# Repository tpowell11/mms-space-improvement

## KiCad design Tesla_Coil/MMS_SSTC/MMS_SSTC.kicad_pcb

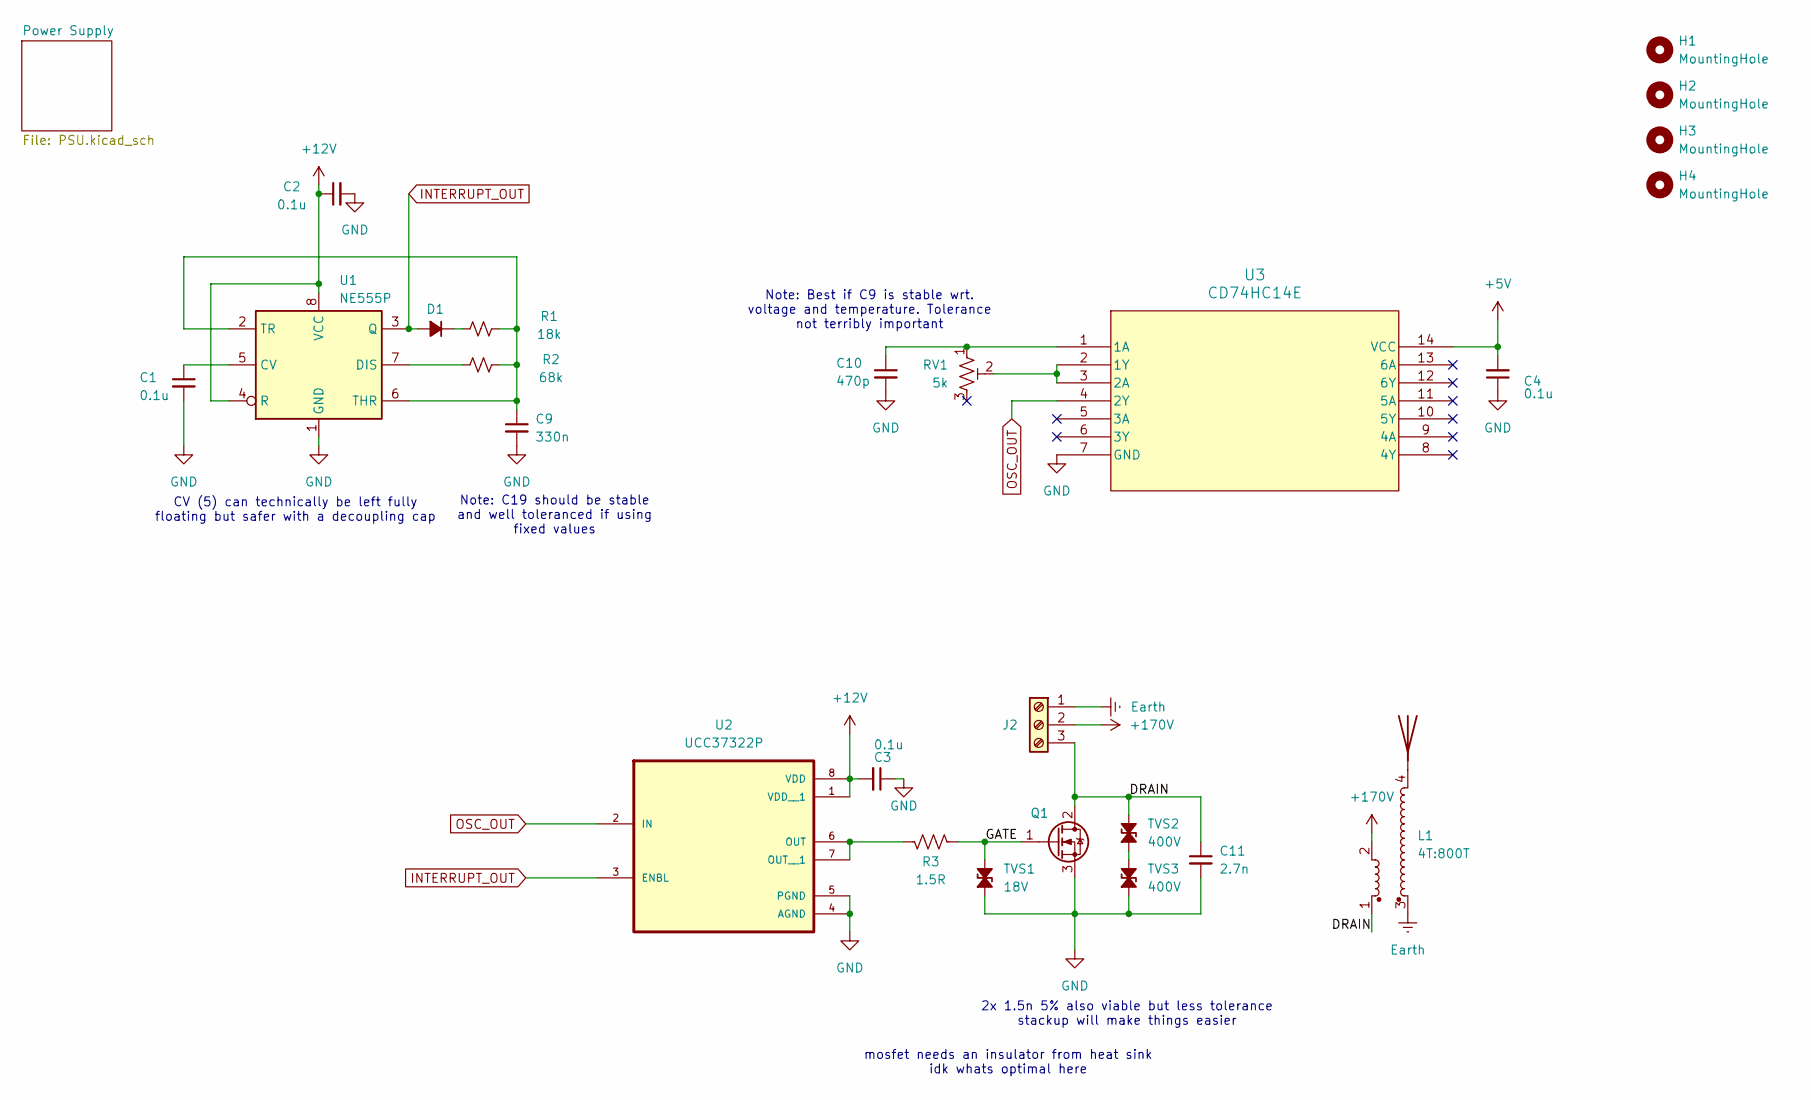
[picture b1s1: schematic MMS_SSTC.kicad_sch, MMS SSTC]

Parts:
AE1: Antenna
C1, C2, C3, C4: 0.1u; C_Disc_D3.0mm_W2.0mm_P2.50mm
C9: 330n; C_Rect_L7.2mm_W3.5mm_P5.00mm_FKS2_FKP2_MKS2_MKP2
C10: 470p; C_Rect_L7.2mm_W4.5mm_P5.00mm_FKS2_FKP2_MKS2_MKP2
C11: 2.7n; C_Rect_L13.0mm_W4.0mm_P10.00mm_FKS3_FKP3_MKS4
D1: D_Small_Filled; D_DO-35_SOD27_P7.62mm_Horizontal
H1, H2, H3, H4: MountingHole; MountingHole_3.2mm_M3
J2: Screw_Terminal_01x02; 691137710003
L1: 4T:800T
Q1: FQA8N100C; TO-247-3_Vertical
R1: 18k; R_Axial_DIN0204_L3.6mm_D1.6mm_P5.08mm_Horizontal
R2: 68k; R_Axial_DIN0204_L3.6mm_D1.6mm_P5.08mm_Horizontal
R3: 1.5R; R_Axial_DIN0204_L3.6mm_D1.6mm_P5.08mm_Horizontal
RV1: 5k; Potentiometer_Bourns_3296X_Horizontal
TVS1: 18V; D_DO-27_P12.70mm_Horizontal
TVS2, TVS3: 400V; D_DO-27_P12.70mm_Horizontal
U1: NE555P; DIP-8_W7.62mm_Socket
U2: UCC37322P; DIP-8_W7.62mm_Socket
U3: CD74HC14E; DIP-14_W7.62mm_Socket

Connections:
+5V: C4.2, U3.14 (VCC); also elsewhere on the board
+12V: C2.1, C3.2, U1.4 (R), U1.8 (VCC), U2.1 (VDD__1), U2.8 (VDD); also elsewhere on the board
+170V: J2.2, L1.2; also elsewhere on the board
/DRAIN: C11.1, J2.3, L1.1, Q1.2 (D), TVS2.2 (A2)
/GATE: Q1.1 (G), R3.1, TVS1.2 (A2)
Earth: J2.1, L1.3; also elsewhere on the board
GND: C1.2, C2.2, C3.1, C4.1, C9.2, C10.2, C11.2, Q1.3 (S), TVS1.1 (A1), TVS3.1 (A1), U1.1 (GND), U2.4 (AGND), U2.5 (PGND), U3.7 (GND); also elsewhere on the board
INTERRUPT_OUT: D1.2 (A), U1.3 (Q), U2.3 (ENBL)
unnamed: AE1.1, L1.4
unnamed: D1.1 (K), R1.1
unnamed: TVS2.1 (A1), TVS3.2 (A2)
unnamed: C1.1, U1.5 (CV)
unnamed: R2.1, U1.7 (DIS)
unnamed: C9.1, R1.2, R2.2, U1.2 (TR), U1.6 (THR)
unnamed: R3.2, U2.6 (OUT), U2.7 (OUT__1)
unnamed: C10.1, RV1.1, U3.1 (1A)
unnamed: RV1.2, U3.2 (1Y), U3.3 (2A)
OSC_OUT: U2.2 (IN), U3.4 (2Y)

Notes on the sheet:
mosfet needs an insulator from heat sink idk whats optimal here
2x 1.5n 5% also viable but less tolerance stackup will make things easier
Note: C19 should be stable and well toleranced if using fixed values
Note: Best if C9 is stable wrt. voltage and temperature. Tolerance not terribly important
CV (5) can technically be left fully floating but safer with a decoupling cap

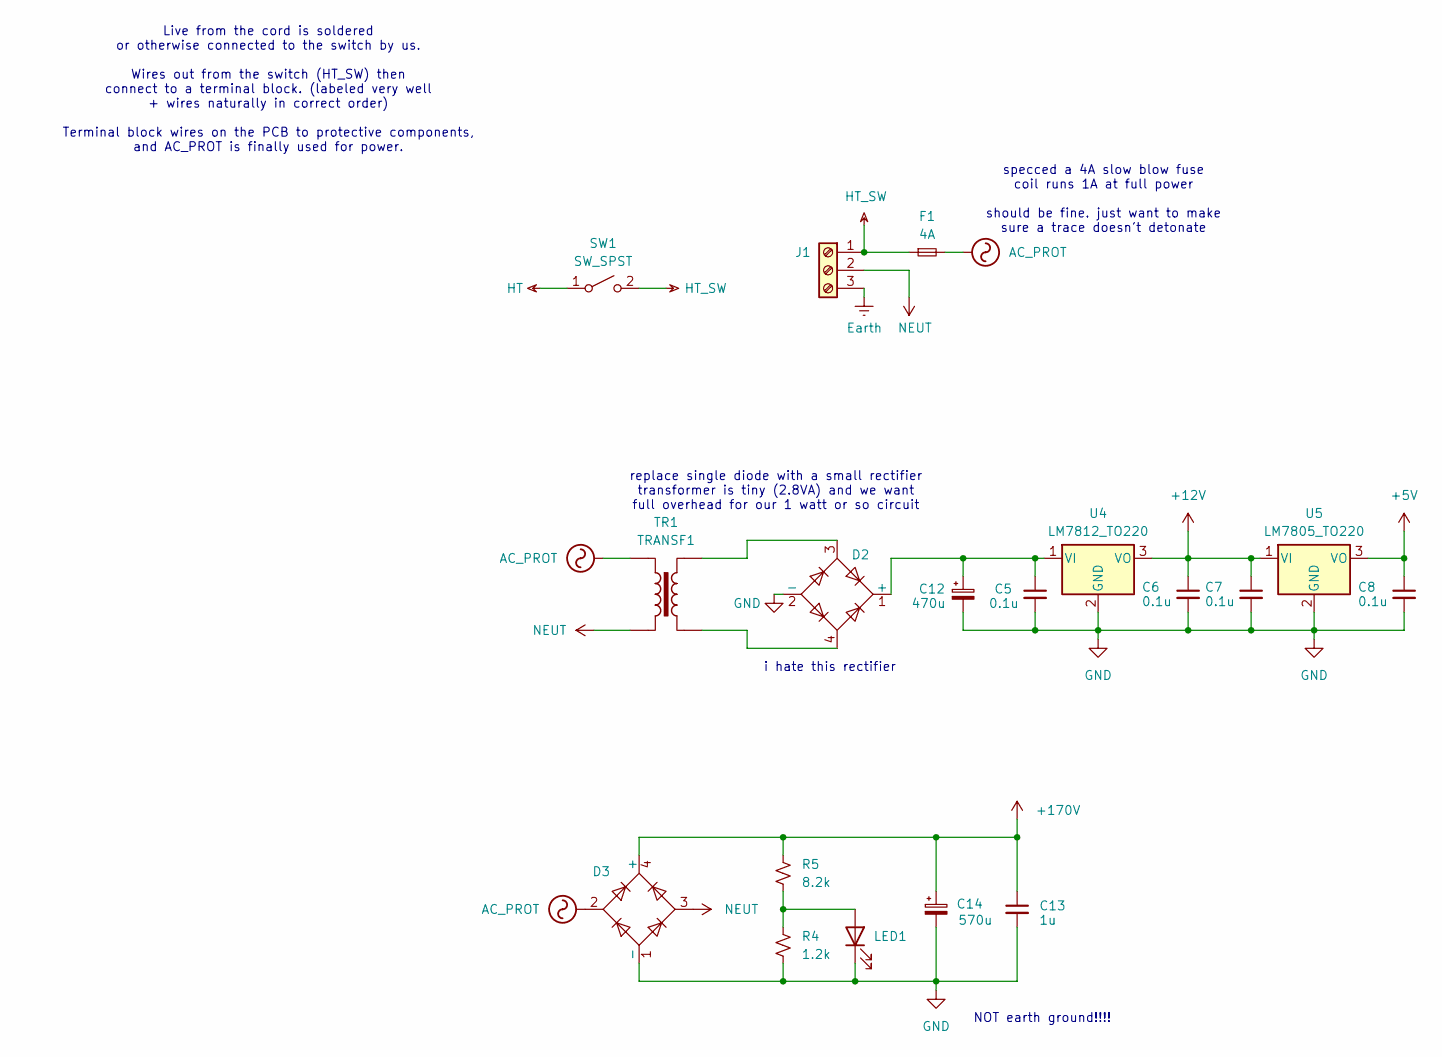
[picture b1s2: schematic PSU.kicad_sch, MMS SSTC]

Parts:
C5, C6, C7, C8: 0.1u; C_Disc_D3.0mm_W2.0mm_P2.50mm
C12: 470u; CP_Radial_D12.5mm_P5.00mm
C13: 1u; C_Rect_L18.0mm_W7.0mm_P15.00mm_FKS3_FKP3
C14: 570u; CP_Radial_D30.0mm_P10.00mm_SnapIn
D2: DB105; Diode_Bridge_DIP-4_W7.62mm_P5.08mm
D3: B125C2300-1500A; Diode_Bridge_Vishay_GBL
F1: 4A; R_Axial_DIN0411_L9.9mm_D3.6mm_P12.70mm_Horizontal
J1: Screw_Terminal_01x02; 691137710003
LED1: LED; LED_D3.0mm_Horizontal_O1.27mm_Z2.0mm
R4: 1.2k; R_Axial_DIN0204_L3.6mm_D1.6mm_P5.08mm_Horizontal
R5: 8.2k; R_Axial_DIN0617_L17.0mm_D6.0mm_P5.08mm_Vertical
SW1: SW_SPST
TR1: TRANSF1; Transformer_Zettler_BV301S18028
U4: LM7812_TO220; TO-220-3_Vertical
U5: LM7805_TO220; TO-220-3_Vertical

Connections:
+5V: C8.1, U5.3 (VO); also elsewhere on the board
+12V: C6.1, C7.1, U4.3 (VO), U5.1 (VI); also elsewhere on the board
+170V: C13.1, C14.1, D3.4 (+), R5.1; also elsewhere on the board
AC_PROT: D3.2, F1.2, TR1.1
Earth: J1.3; also elsewhere on the board
GND: C5.2, C6.2, C7.2, C8.2, C12.2, C13.2, C14.2, D2.2 (-), D3.1 (-), LED1.1 (K), R4.2, U4.2 (GND), U5.2 (GND); also elsewhere on the board
HT_SW: F1.1, J1.1, SW1.2 (B)
NEUT: D3.3, J1.2, TR1.2
unnamed: C5.1, C12.1, D2.1 (+), U4.1 (VI)
unnamed: D2.3, TR1.4
unnamed: D2.4, TR1.3
unnamed: LED1.2 (A), R4.1, R5.2

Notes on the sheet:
NOT earth ground!!!!
i hate this rectifier
Live from the cord is soldered or otherwise connected to the switch by us. Wires out from the switch (HT_SW) then connect to a terminal block. (labeled very well + wires naturally in correct order) Terminal block wires on the PCB to protective components, and AC_PROT is finally used for power.
replace single diode with a small rectifier transformer is tiny (2.8VA) and we want full overhead for our 1 watt or so circuit
specced a 4A slow blow fuse coil runs 1A at full power should be fine. just want to make sure a trace doesn't detonate

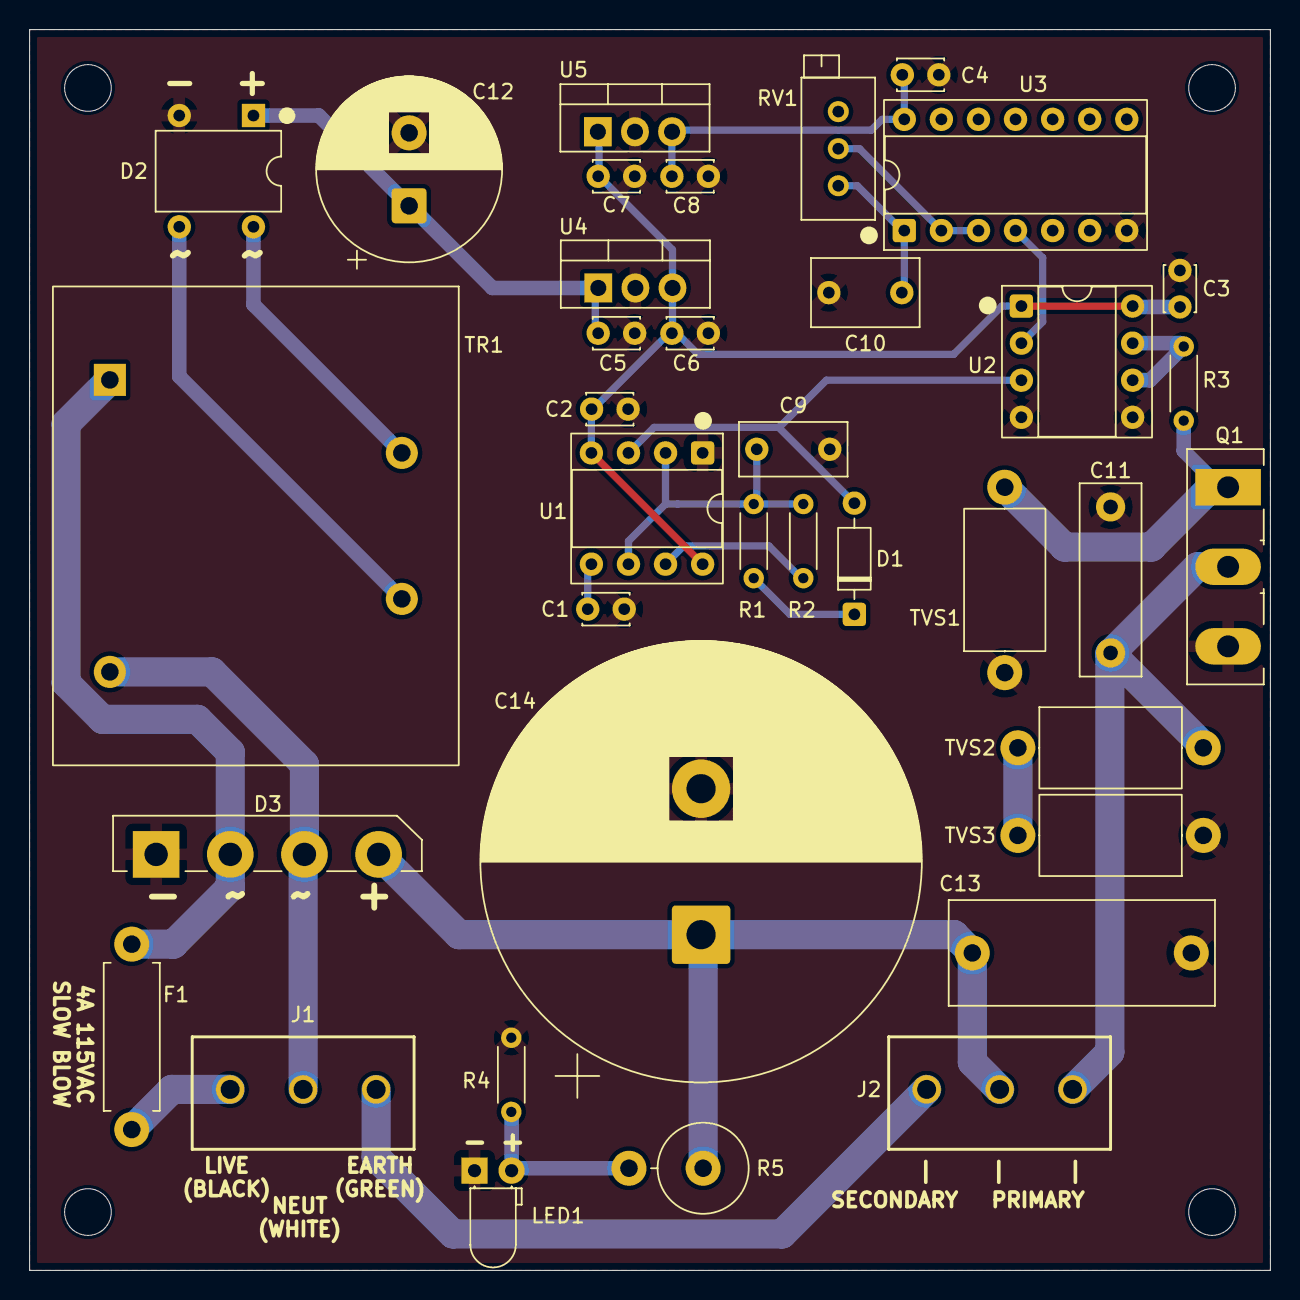
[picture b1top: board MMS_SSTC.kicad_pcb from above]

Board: 2 copper layers, 85.0 x 85.0 mm, 41 parts (0 on the bottom side), 24 nets.

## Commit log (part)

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2024-11-01 importing old projects, enclosure work.
2024-11-02 apartment updates, handle first revision
2024-11-02 apartment updates: moved to pin based lock-open for cost and saftey reasons
2024-11-04 increase interface depth, handle diameter, and handle depth
2024-11-06 modifications to pull
2024-12-06 Created handle V2 and temporary magnet holder
2024-12-07 Generated .3mf for production set of 4 handles
    Also I added temp files and FEA results to the .gitignore because otherwise that WILL cause problems one of these days and then I will be killed with hammers. :3
2025-01-06 Window Marker Holder Thingy
    You wanted a "5 picosecond design" so uhhh these are probably good enough?
2025-01-06 added toolcart lables to the repo
2025-01-08 door hooks up
2025-01-08 Started designing Made@Mines voting box
    It is NOT DONE YET. I am still working on it.
2025-01-09 MINI spool holder I guess
    HEXAGONS YIPPEE
2025-01-13 short filament holders
2025-01-15 Printer maintenance stuff
2025-01-15 Fixed the fidget cube 3mfs
2025-01-15 Fixed versioning of Hinge V3.3 and Handle V2.0
    Also removed some more deprecated 3mf files and fixed a few relations.
2025-01-15 Removed temporary magnet holder and old spool holder
    The temporary magnet holder was bad and is not needed now that we have most of the handles printed anyways. Also for some reason there was the OLD version of the spool holder that doesn't have the he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
2025-01-15 Created 3mf for set of top handles
2025-01-19 Added handles to printer enclosure assemblies
    I also fixed and organized some mates, removed the aluminum trim from the doors, and redid some naming conventions so names make more sense. To me.
    I mean also I think to most people because the door configuration labeled "Right Top" is for the top right corner of a printer enclosure. It just means that the HANDLE for the top right door is then 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
2025-01-19 Fixed handles on printer enclosure storage door assemblies
    I accidentally used the Handle V2.0 PART not the Handle V2.0 Assembly so it didn't have the magnets in it and also a bit of other weirdness. I replaced it with the assembly so it's fine now but oops.
2025-01-19 Added screws to printer enclosure assemblies
2025-01-27 Worked on Made@Mines voting box some more
2025-01-27 Worked on Made@Mines voting box even more
2025-01-27 Added new softjaw model for vise
2025-01-28 Made At Mines taller voting box with side plates
2025-01-28 Tweaked softjaws for better fit
2025-02-01 Temporary whiteboard marker holder for printer wall!
    This is TEMPORARY! I will eventually go back and design a new better one that also works nicely with the printer wall trim but like we don't need that for now so I'm not going to spend several hours 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
2025-02-01 Created Filament Swatch stuff
2025-02-02 Generated Rolodex parts for filament swatches
2025-02-03 Designed new tall printer shelves for enclosed XL
    There is now Tall Printer Frame V2a which drops the XL by only 2 pegs so it has exactly enough vertical clearance but removes the space for more i3-sized printers at the base of the shelves. There is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
2025-02-03 Created production print files for filament rolodex
2025-02-03 Fixed and rebuilt Printer Wall V2a
2025-02-03 Selected Printer Wall V2b
    Removed deprecated components for Printer Wall V1 and V2a
2025-02-03 Updated printer wall doors
    Storage doors are now black polycarbonate instead of wood and also the tall printer frames now have the short storage doors at the bottom.
2025-02-04 Started designing side panels for printer wall
2025-02-04 More rolodex parts
    This time it's the rolodex spacers. Also I renamed the folder full of gcode files.
2025-02-14 Voting box V2.3 test print
    I adjusted the side plates to use a dovetail locking design and also just generally made the slice settings better.
2025-02-15 Added resin scraper
2025-02-15 Sliced filament swatches for more colors
2025-02-15 Sliced print files for Single Use Scraper
2025-02-15 Packed more Single Use Scrapers onto a bed
2025-02-22 Made At Mines - Voting Box V2.3.3 PROTOTYPE
    If this test print goes well then we will begin full production on voting boxes IMMEDIATELY.
2025-02-23 THE LOGO
    I mean, kinda. There's the SVG and PNG version of the fixed logo,
    some color calibration stuff, a link to the Desmos graph I used to get measurements and stuff, and a few other things, but the SVG isn't the best because the colors aren't set as variables but also w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
2025-02-28 Added Made@Mines logo vectors
2025-03-09 Started designing TV remote holder
2025-03-10 Generated more filament swatches
2025-03-10 Generated a few more swatch print files
2025-03-10 Add files for posters. Drafting then final design will be done in latex
2025-03-10 Progress on workshop poster creation
2025-03-10 combinatorial workshop poster explosion
2025-03-10 Workshop poster final draft finished
2025-03-10 Saved poster file
2025-03-11 Color tweaks to workshop poster background
2025-03-11 Workshop posters complete
2025-03-12 Added SAIL approved workshop posters
2025-03-12 Updated GIMP template for better PDF exports
2025-03-13 Tweaked the leatherworking date
2025-03-19 Updated side plates for Made At Mines boxes
2025-03-19 Added token model files
    The token model files were previously in Teams Narnia (Events and Workshops Channel -> Files Tab -> Made@Mines -> Marketing Materials) so now everything should mostly be in one place I think?
2025-03-20 Removed deprecated voting box files
    Current voting box version is V2.3.5 with body production files and side plate prototype files.
2025-03-20 Created production file for voting box side plates
    This file has not actually been run yet and may require some changes after the prototype has been run and inspected, but if the prototype does work well then we'll have this ready to go.
2025-03-20 Add made@mines materials that were floating in my pictures folder
2025-03-22 Update to M@M banner SVG (idk what exactly)
2025-03-23 Add Luis's filament guide attachment blocks
2025-03-25 Experimental QR code fidget cubes print file
2025-03-25 Updated closed ecosystem workshop poster. Updated Made@Mines general poster. Both should be final.
2025-03-25 Updated .gitignore to prevent Dolphin .directory files showing up
2025-03-25 Migrated all Made@Mines posters to the Teams. Avoid using Git for posters in the future.
2025-03-25 Migrated workshop posters to Teams
2025-03-25 Modified QR fidged cube prototype
2025-03-25 Edited QR fidget cube to fix top layers
2025-03-27 Updated QR cube prototype to print upper code successfully
2025-04-04 Cubes for OSL and stuff
    I think Layne and I might have had a different V2.4(.0) so uhhh I will need to look through that and make sure I didn't accidentally nuke something and also a bunch of old cube versions are now no lo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
2025-04-05 Modified token design to production ready version
2025-04-06 Added replacement leg for dress form
2025-04-06 THE SIDE PLATES PLEASE FIT
2025-04-06 Updated dress form leg to fit on an i3
2025-04-07 Started work on foundation M's
2025-04-07 foundation m sent to foundation for physical approval
2025-04-07 oops
2025-04-07 the 3mf
2025-04-10 Add made@mines token counting cylinders
2025-04-16 Updated OSL fidget cube print files
2025-04-16 Moved OSL Fidget Cubes and deleted some deprecated files
    YES I KNOW THE FILES ARE A MESS AND I SHOULDN'T BE DOING VERSION NUMBERS AT ALL BECAUSE IT'S GITHUB. I WILL BE REORGANIZING THE ENTIRE REPOSITORY OVER SUMMER AND ALSO DELETING/RENAMING EVERY SINGLE O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
2025-04-16 Updated gcode so the XL maybe stops exploding
    Old gcode V2.4.3 is kept around for comparison just in case that's the problem. Also we updated the XL firmware from 6.2.2 to 6.2.4 so maybe it'll stop giving extruder motor errors???
2025-04-20 remove large file
2025-04-21 v3.0.0 testing good, moving on to production
2025-04-21 foundation m ready for testing
2025-05-02 begin foundation prod testing
2025-05-03 Removed brims from production Ms
2025-05-14 Remodeled space lock ready for validation
2025-05-14 Update space lock to final design
2025-05-15 modify space lock stop to final dimensions
2025-05-15 renamed folder
2025-05-25 Create SSTC project for fall welcome
2025-05-27 Adapt LabCoatz Driverless SSTC circuit. Capacitive ballast design still needs work.
2025-05-28 update gitignore
2025-05-28 nuke the kicad .zip files
2025-06-06 Updated vise softjaws 3MF to include settings
2025-06-11 Added new door decals
2025-06-24 Finish initial shopping list for steve ward class E design
2025-06-24 Progress save for modification on schematic. Nowhere near done
2025-06-24 Create frame for coil parts for prototyping
2025-07-02 Updated schematic for prototype PCB - needs DKPNs and final review still
2025-07-02 Update supporting files for schematic oops
2025-07-03 Minor tweaks to schematic, needs finished and all details added
2025-07-04 Finish SSTC prototype schematic, needs PCB
2025-07-05 Begin work on SSTC prototype PCB
2025-07-07 Finish SSTC prototype PCB
2025-07-09 Commit minor changes to SSTC
2025-07-11 Start work on SSTC power supply
2025-07-13 Commit additions to SSTC PSU schematic
2025-07-25 Begin work on final tesla coil design
2025-07-27 Finish coil winder parts
2025-07-28 Add changes to tesla coil schematic and coil winder parts
2025-07-28 Draft BOM for final SSTC design
2025-07-29 apply cost saving measures
2025-07-31 Rough layout on final SSTC PCB
2025-07-31 Commit progress on final SSTC board
2025-07-31 route SSTC PCB and then find out critical problem yay
2025-08-02 case design v1
2025-08-02 FINISH THE DAMN THING
2025-08-02 text variations
2025-08-02 SSTC PCB finished
2025-08-05 Create M-Climb tokens
2025-08-05 Add solidworks compatible logo DXF
2025-08-05 Update incorrect capacitor on tesla coil
2025-08-06 Modifications to SSTC case for production
2025-08-07 Draft up tesla coil workshop presentation
2025-08-08 Hopefully penultimate changes to SSTC case
2025-08-09 Finalize case
2025-08-15 Tesla coil heatsink design
2025-08-15 marking tools
2025-08-16 Stupid heatsink CAM that didn't work
2025-08-16 tuning driver sliced
2025-08-16 Heatsink Plate Cutting Jig V1
2025-08-16 driver addmf
2025-08-23 work on new case
2025-08-23 for real this time
2025-08-26 finish acrylic case minus final tolerances
2025-08-28 Add new corner pieces for M3 hex, adjust acrylic thickness
2025-08-28 Add updated soldering step images
2025-09-01 make it use a vishay trimpot fuck you bourns
2025-09-28 Stupid tesla coil flow sim stuff
    I don't really want to completely nuke these files so I deleted all the simulation results and left the configuration stuff alone. It should all be small enough to not cause problems now and if it do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
2025-09-28 Update vise-softjaw.3MF
    I don't know why this file is insisting there's changes but it won't let me discard the changes and I don't think much happened anyways???
2025-09-28 Blaster Design Factory model
    Uploaded 2024-02 model of the BDF. Some stuff has been moved around from this proposal but it is mostly accurate still.
2025-09-28 Added furniture
    Specifically the lockers, computer desk, and vinyl cutter to the big model of the BDF.
2025-10-26 work
2025-10-27 clone fix
2025-10-29 Printer Apartment Lock Mounts
2025-11-04 Resin tools + fan grill
    Resin printer tools (Funnels) and fan grill for the vent
2025-11-21 Space Improvement
    Various space improvement files.
2025-12-02 FILAMENT SIGNS
    HOPEFULLY THIS IS GOOD ENOUGH OKAY COOL ANYWAYS MOVING ON NOW
2026-01-20 Battery holders
    More battery holders
2026-02-08 Air compressor
    muffler added
2026-03-10 add trophy stars from paper plane competition
2026-05-16 Add container for no. 2 xacto blades
2026-05-16 Move SSTC files to separate repo
